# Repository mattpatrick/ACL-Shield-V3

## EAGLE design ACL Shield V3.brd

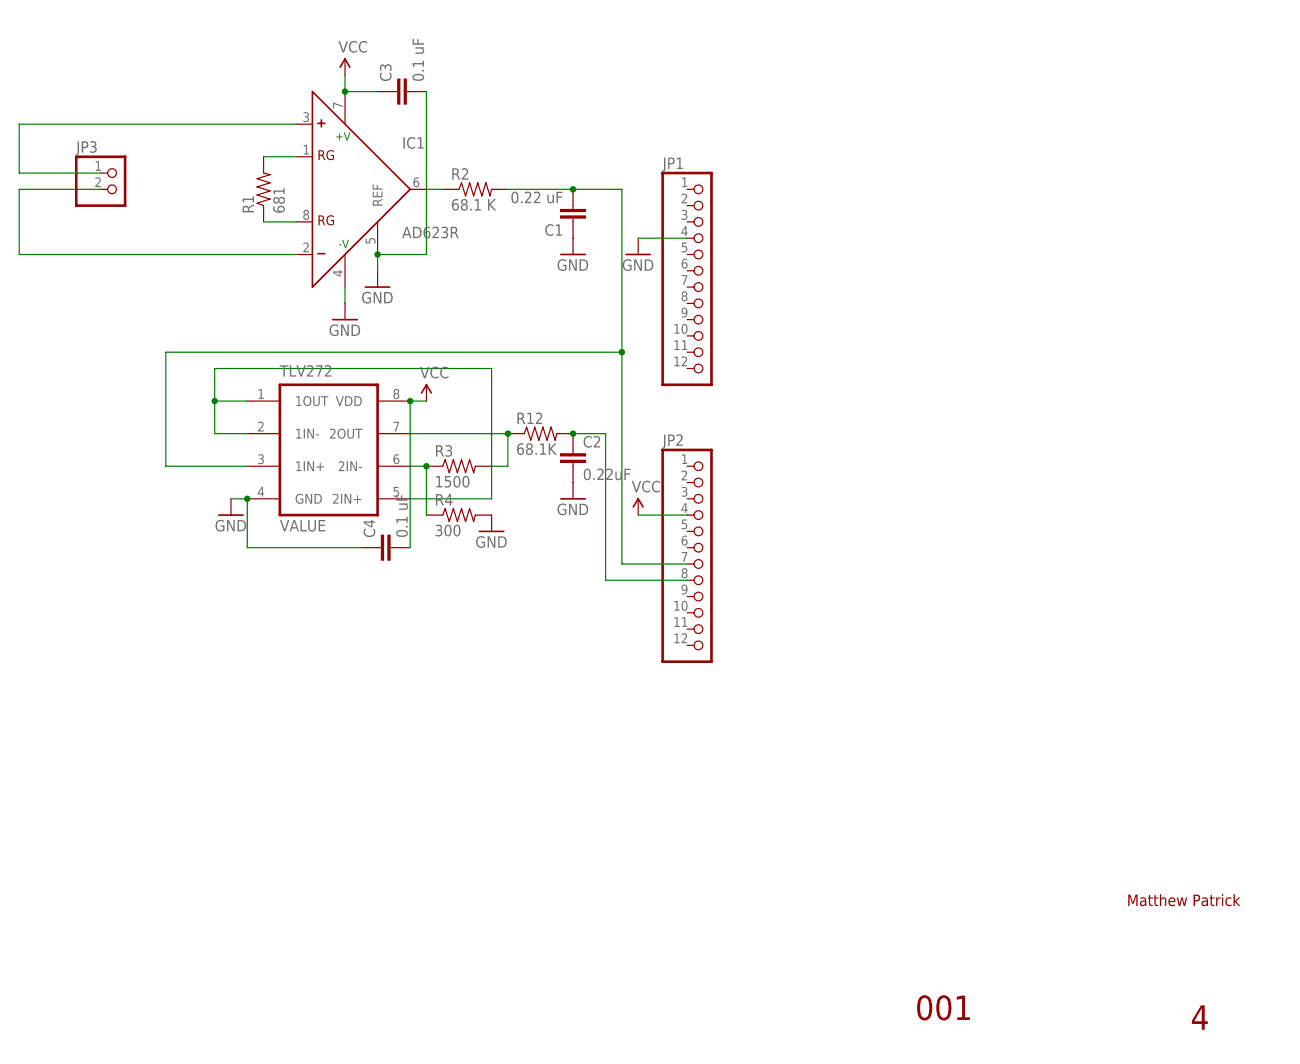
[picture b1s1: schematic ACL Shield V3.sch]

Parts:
C1: 0.22 uF; 0603-CAP
C2: 0.22uF; 0603-CAP
C3, C4: 0.1 uF; 0603-CAP
IC1: AD623R; SO8
JP1, JP2: PINHD-1X12; 1X12
JP3: PINHD-1X2; 1X02
R1: 681; 0603-RES
R2: 68.1 K; 0603-RES
R3: 1500; 0603-RES
R4: 300; 0603-RES
R12: 68.1K; 0603-RES
U$2: T2721; SO-08

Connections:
GND: C1.1, C2.2, C3.2, C4.1, IC1.4 (-V), IC1.5 (REF), JP1.4, R4.2, U$2.4 (GND)
unnamed: IC1.1 (RG), R1.2
unnamed: IC1.8 (RG), R1.1
unnamed: C1.2, JP2.7, R2.2, U$2.3 (1IN+)
unnamed: IC1.6 (OUT), R2.1
unnamed: U$2.1 (1OUT), U$2.2 (1IN-), U$2.5 (2IN+)
unnamed: R3.1, R4.1, U$2.6 (2IN-)
unnamed: R3.2, R12.1, U$2.7 (2OUT)
unnamed: IC1.2 (-), JP3.2
unnamed: C2.1, JP2.8, R12.2
unnamed: IC1.3 (+), JP3.1
VCC: C3.1, C4.2, IC1.7 (+V), JP2.4, U$2.8 (VDD)

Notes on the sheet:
Matthew Patrick
001

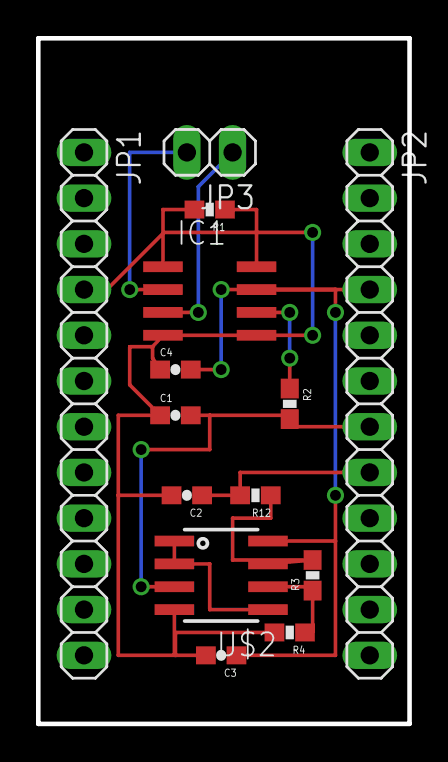
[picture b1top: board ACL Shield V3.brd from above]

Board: 2 copper layers, 20.6 x 38.1 mm, 14 parts (0 on the bottom side), 12 nets.

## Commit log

2013-10-24 ACL Shield V3 First Commit
2013-10-24 Added .gitignore

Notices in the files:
parts and their libraries:
SparkFun: Licensing: CC v3.0 Share-Alike You are welcome to use this library for commercial purposes.
